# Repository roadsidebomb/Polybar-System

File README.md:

<br/>
<div align="center">

</div>

# The Polybar System
**3D Printable Guitar Controllers!**

The Polybar project, by Three Pieces Controllers, is a modular 3D printable controller system for music games like YARG, Clone Hero, and others.

This GitHub page is for downloading order-ready gerbers files and archiving previous versions of the Polybar.
Please see the [archive branch here](https://github.com/roadsidebomb/Polybar-System/tree/archive) for legacy project downloads.
  
You can find the latest version of the print files and build guide at [our Printables page](https://www.printables.com/model/277183-polybar-system-3d-printed-guitar-controllers). Printables download includes the print ready STL files and the complete build guide!

## 🎧 Discord 

For extra resources, such as the component shopping list, join our Discord server! We'd be happy to help if you need assistance with your controller build or firmware.<br/>
[Join us on Discord!](https://discord.gg/2qrFx3mJ9F)

## 🔨 Contributing

If you have ideas for a new project, or existing ones, drop us a line at the Discord link above. It's our main development hub.

## 💸 Buy a Controller or Solderless Kit

Don't have a 3D printer, or want to buy all of the parts yourself?
You can find complete controllers, solderless kits, and accessories from our official store, and our worldwide partner vendors.

[Official Three Pieces Controllers Shop](https://threepieces.net/) United States<br/>
[Foucault Customs](https://foucaultcustoms.com.br/) Brazil<br /> 
[RKNZ](https://rknz.nz/ ) New Zealand & Australia<br /> 
[Triple Dee](https://tripledee.co.uk/) United Kingdom & Europe<br /> 
[Pier Printed Products](https://pierprintedproducts.myshopify.com/) United States<br /> 

## 🪪 Credits

roadsidebomb - Creator<br /> 
Pits - Handwire Model Development<br /> 
GetRektRyan - PCB Design and Wireless Support<br /> 
Moose - Build Guide Design<br /> 
PossumOG - PCB Assembly Design<br /> 
MerakiG23 - Animations and Renders<br /> 
HeuristicBishop - PCB Design<br /> 
ptigad - Model Design<br /> 

## 💎 License

This project utilizes the Attribution-NonCommercial-ShareAlike 4.0 International (CC BY-NC-SA 4.0) license.<br /> 
https://creativecommons.org/licenses/by-nc-sa/4.0/<br /> 
You are free to:<br /> 
Share — copy and redistribute the material in any medium or format<br /> 
Adapt — remix, transform, and build upon the material<br /> 
**Under no circumstances are you allowed to use any of the provided materials for commercial works, unless given permission by the owner.**

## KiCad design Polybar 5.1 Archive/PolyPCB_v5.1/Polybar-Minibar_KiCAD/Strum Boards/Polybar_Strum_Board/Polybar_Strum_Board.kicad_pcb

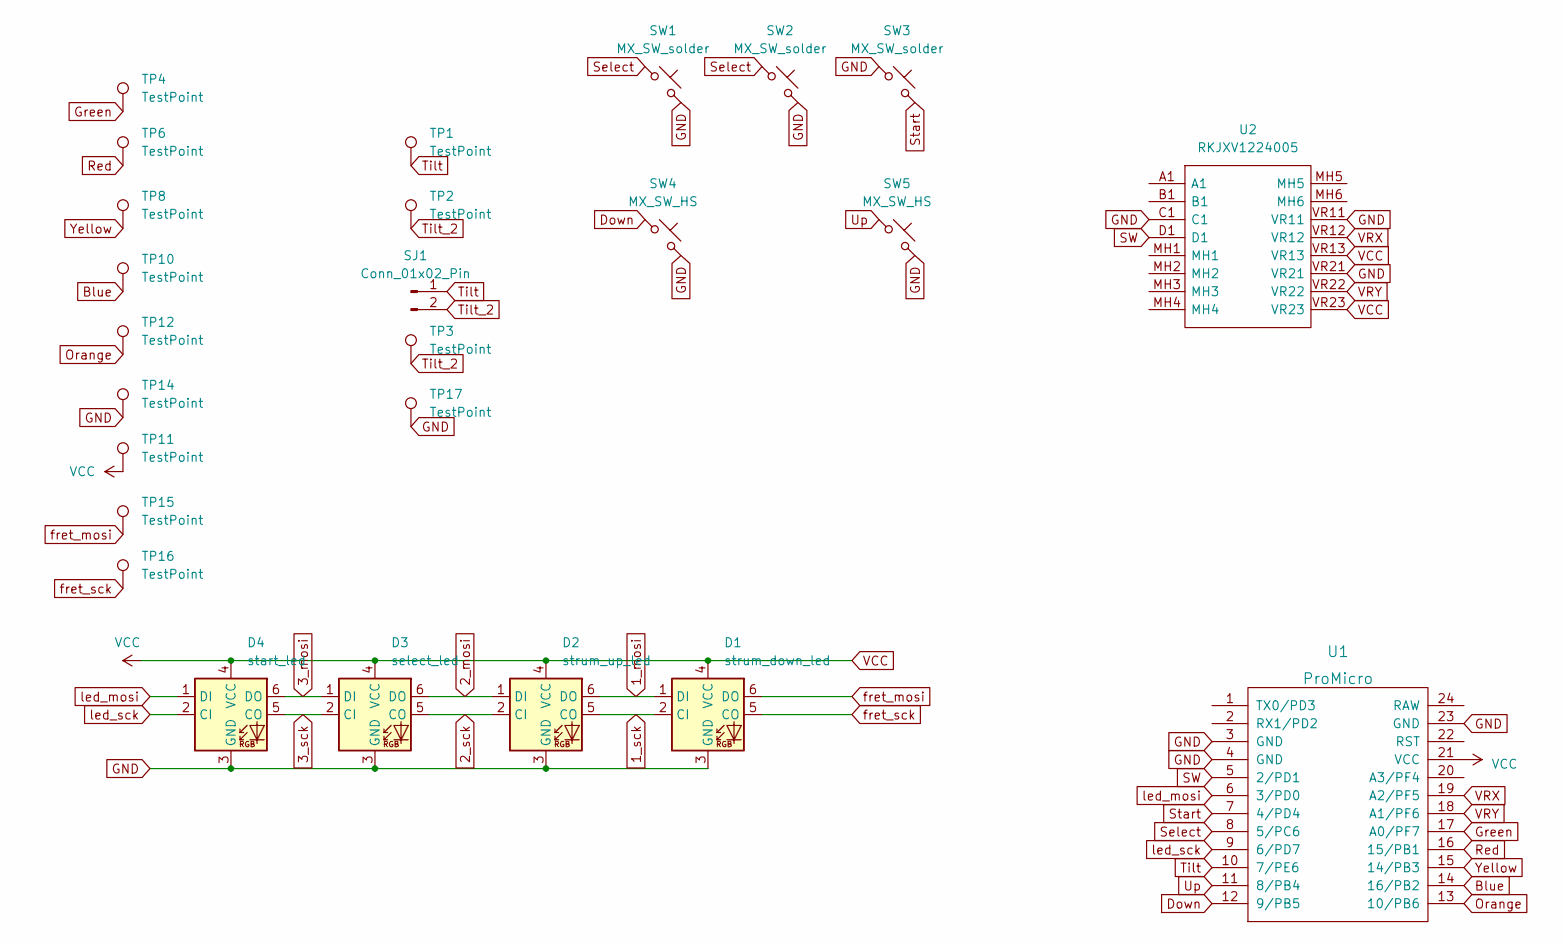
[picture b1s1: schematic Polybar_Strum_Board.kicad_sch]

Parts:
D1: strum_down_led; LED_RGB_5050-6
D2: strum_up_led; LED_RGB_5050-6
D3: select_led; LED_RGB_5050-6
D4: start_led; LED_RGB_5050-6
SJ1: Conn_01x02_Pin; Solder_Jumper
SW1, SW2, SW3: MX_SW_solder; SW_SPST_PTS645
SW4, SW5: MX_SW_HS; Kailh_Hotswap_MX
TP1, TP2, TP3, TP17: TestPoint; test_point_2
TP4, TP6, TP8, TP10, TP11, TP12, TP14, TP15, TP16: TestPoint; test_point
U1: ProMicro; KB2040-ProMicroPins
U2: RKJXV1224005; Manufacturer_Part_Number RKJXV1224005; Mouser Part Number 688-RKJXV1224005

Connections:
1_mosi: D1.1 (DI), D2.6 (DO)
1_sck: D1.2 (CI), D2.5 (CO)
2_mosi: D2.1 (DI), D3.6 (DO)
2_sck: D2.2 (CI), D3.5 (CO)
3_mosi: D3.1 (DI), D4.6 (DO)
3_sck: D3.2 (CI), D4.5 (CO)
Blue: TP10.1, U1.14 (16/PB2)
Down: SW4.1, U1.12 (9/PB5)
GND: D1.3 (GND), D2.3 (GND), D3.3 (GND), D4.3 (GND), SW1.2, SW2.2, SW3.1, SW4.2, SW5.2, TP14.1, TP17.1, U1.3 (GND), U1.4 (GND), U1.23 (GND), U2.C1, U2.VR11, U2.VR21
Green: TP4.1, U1.17 (A0/PF7)
Orange: TP12.1, U1.13 (10/PB6)
Red: TP6.1, U1.16 (15/PB1)
SW: U1.5 (2/PD1), U2.D1
Select: SW1.1, SW2.1, U1.8 (5/PC6)
Start: SW3.2, U1.7 (4/PD4)
Tilt: SJ1.1, TP1.1, U1.10 (7/PE6)
Tilt_2: SJ1.2, TP2.1, TP3.1
Up: SW5.1, U1.11 (8/PB4)
VCC: D1.4 (VCC), D2.4 (VCC), D3.4 (VCC), D4.4 (VCC), TP11.1, U1.21 (VCC), U2.VR13, U2.VR23
VRX: U1.19 (A2/PF5), U2.VR12
VRY: U1.18 (A1/PF6), U2.VR22
Yellow: TP8.1, U1.15 (14/PB3)
fret_mosi: D1.6 (DO), TP15.1
fret_sck: D1.5 (CO), TP16.1
led_mosi: D4.1 (DI), U1.6 (3/PD0)
led_sck: D4.2 (CI), U1.9 (6/PD7)

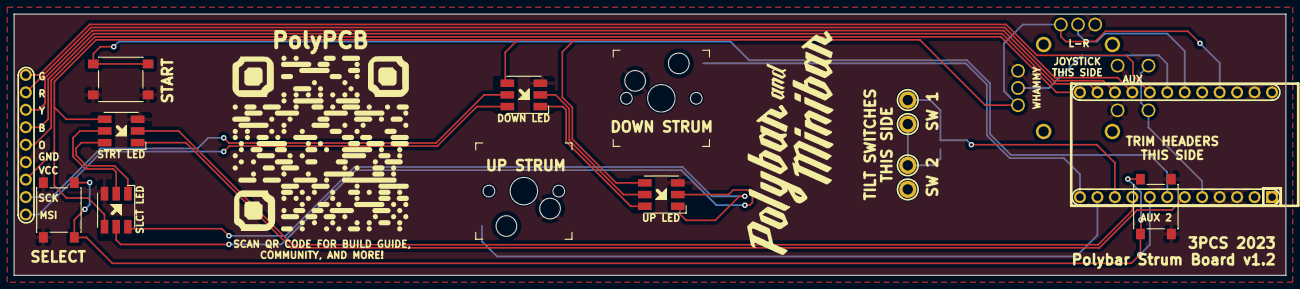
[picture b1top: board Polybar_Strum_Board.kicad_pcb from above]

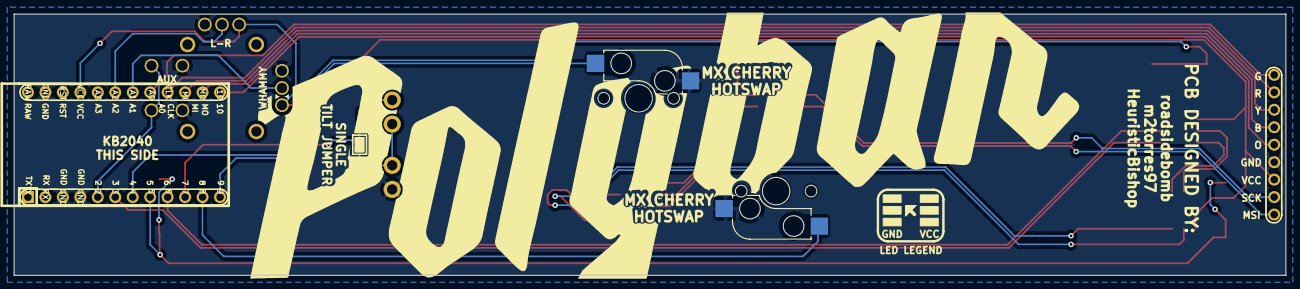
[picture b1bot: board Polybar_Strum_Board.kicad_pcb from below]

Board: 2 copper layers, 185.0 x 38.0 mm, 25 parts (2 on the bottom side), 26 nets.
